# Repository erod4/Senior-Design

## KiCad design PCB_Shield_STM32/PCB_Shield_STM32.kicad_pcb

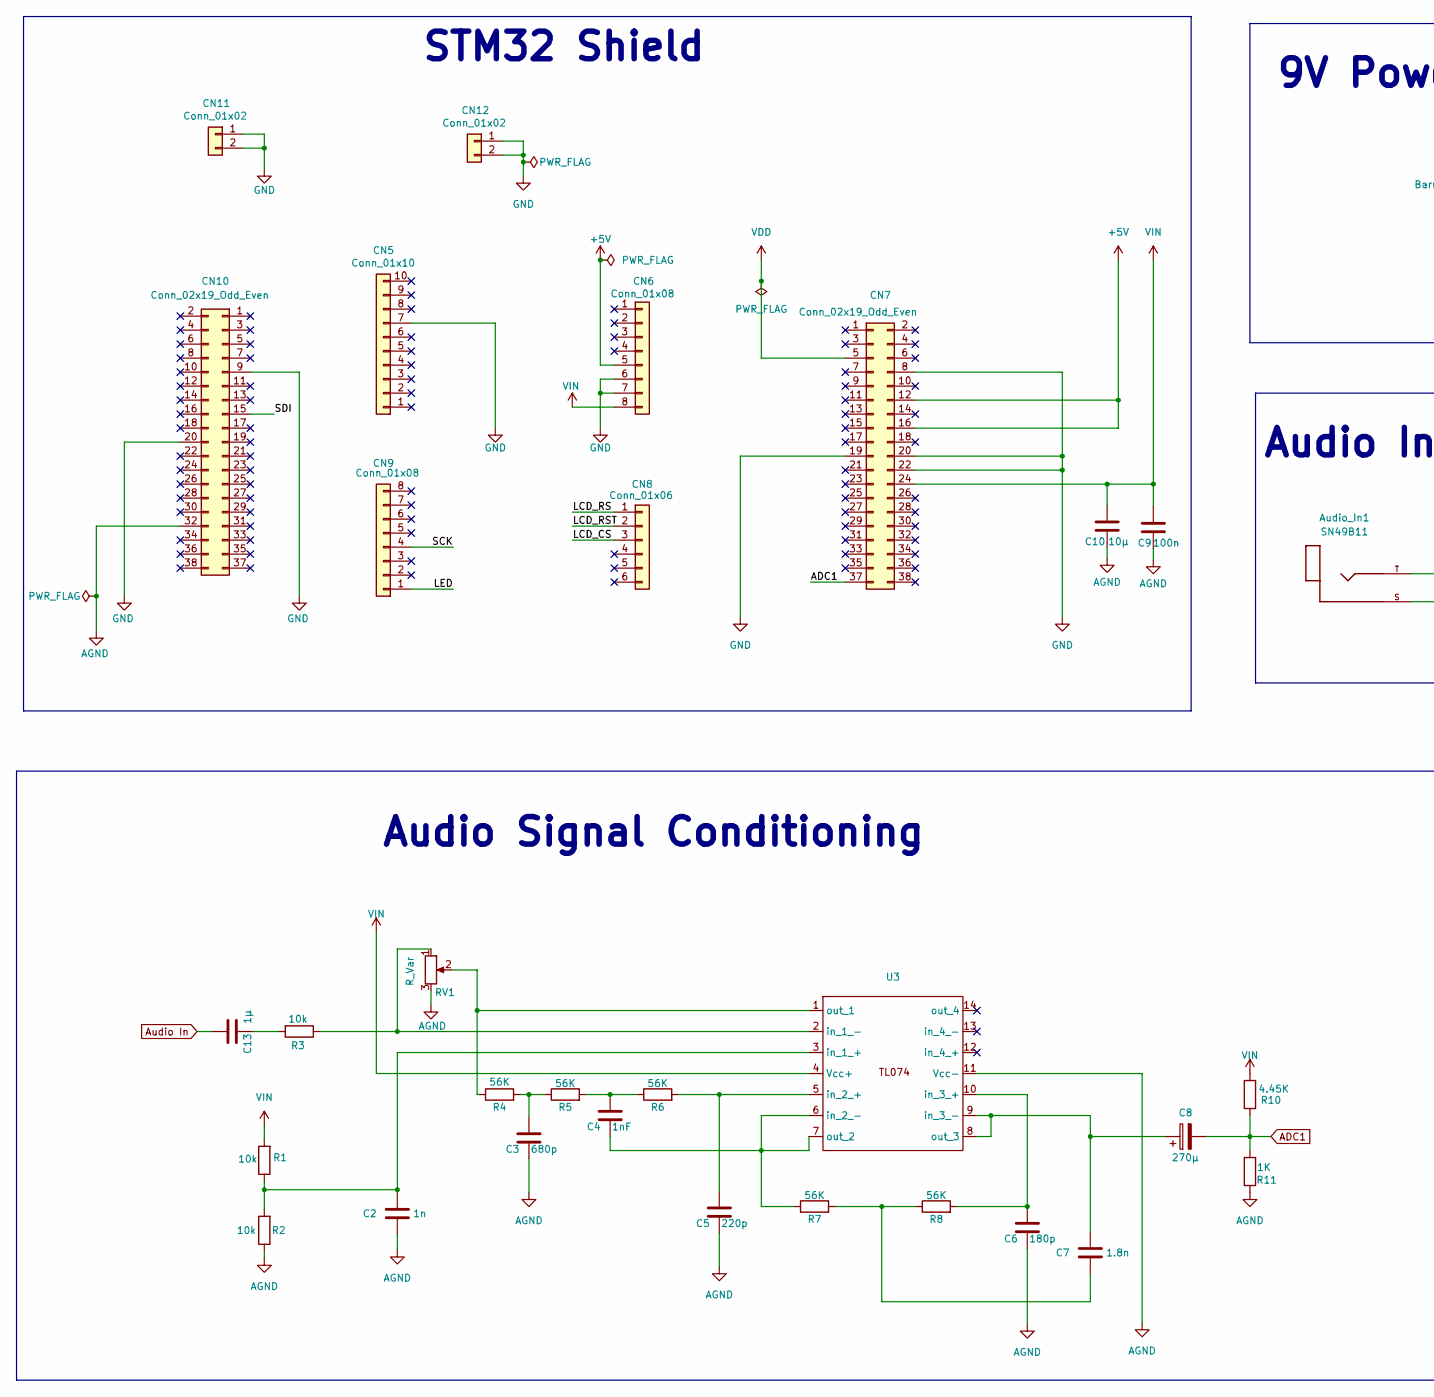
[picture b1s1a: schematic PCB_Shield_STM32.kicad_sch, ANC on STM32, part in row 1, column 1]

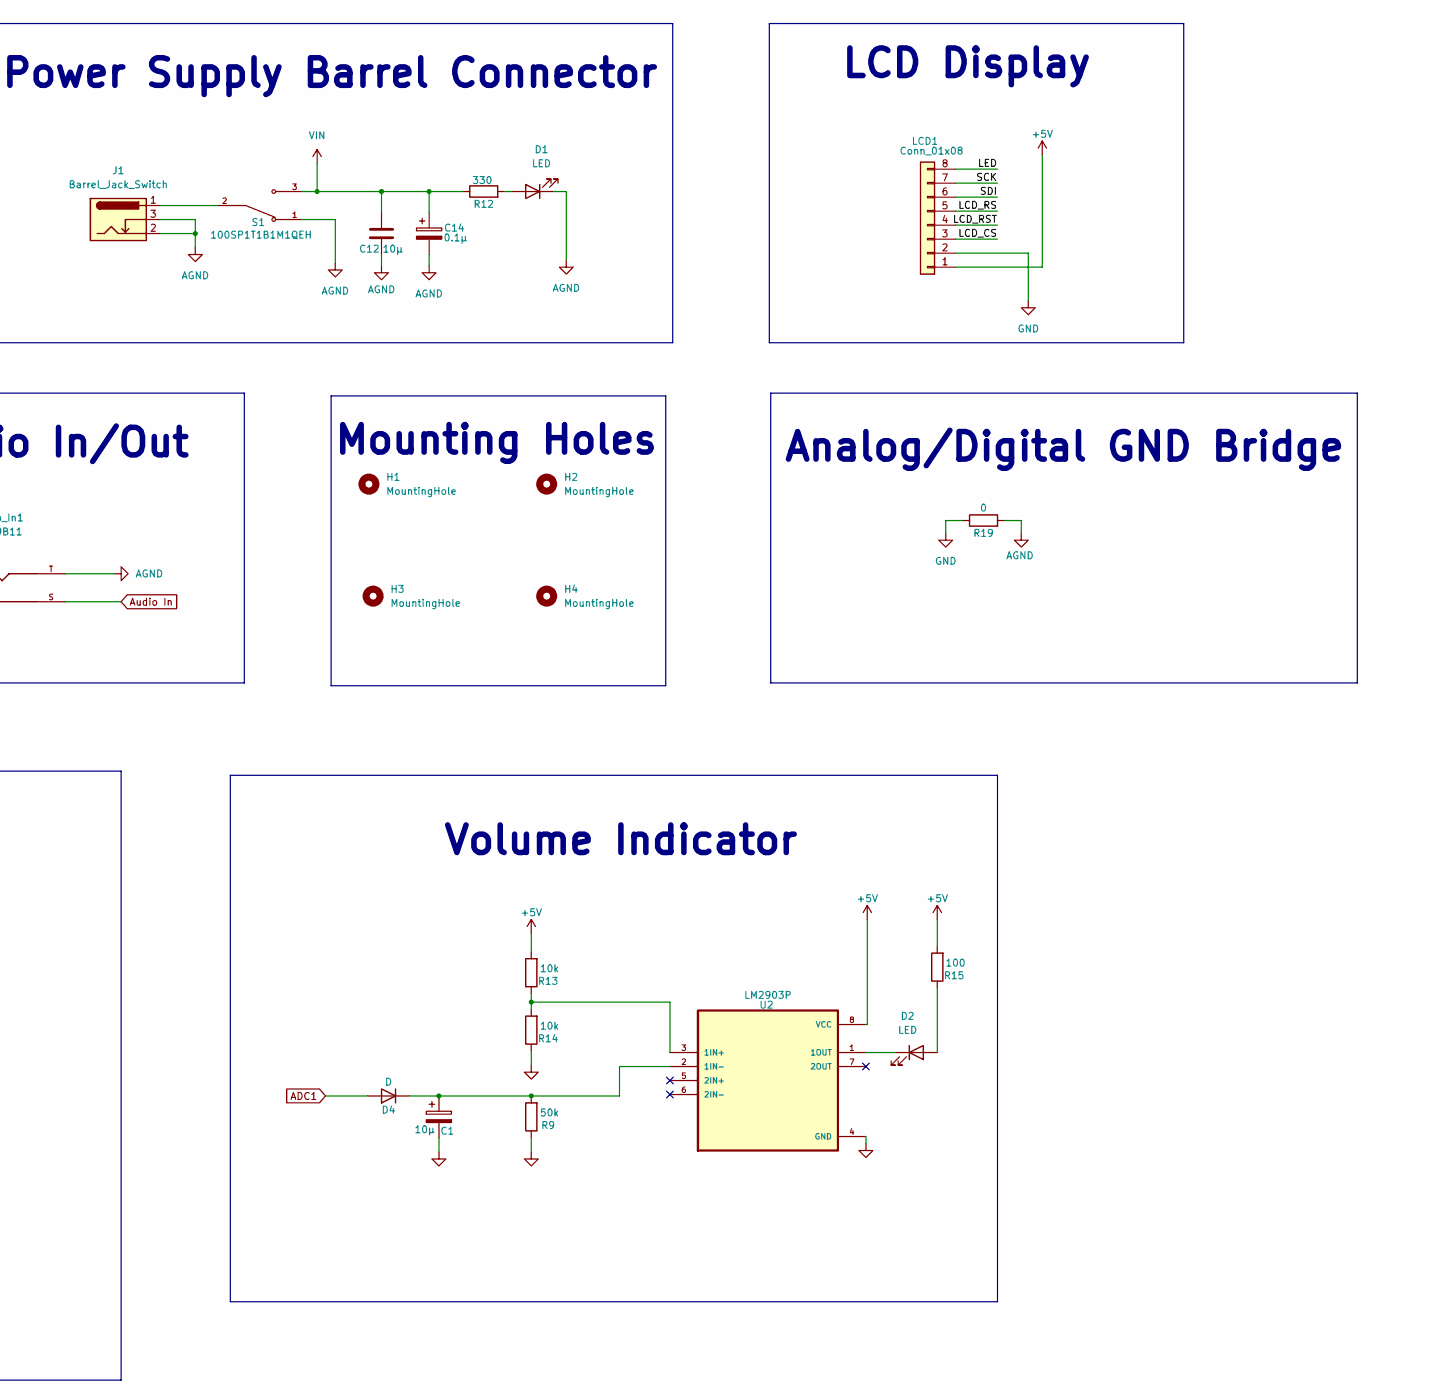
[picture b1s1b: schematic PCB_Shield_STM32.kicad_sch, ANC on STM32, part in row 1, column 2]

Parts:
Audio_In1: SN49B11; SWITCHCRAFT_SN49B11; PARTREV F
C1: 10µ; C_Radial_D4.0mm_H5.0mm_P1.50mm
C2: 1n; C_Disc_D5.0mm_W2.5mm_P5.00mm
C3: 680p; C_Disc_D5.0mm_W2.5mm_P5.00mm
C4: 1nF; C_Disc_D5.0mm_W2.5mm_P5.00mm
C5: 220p; C_Disc_D5.0mm_W2.5mm_P5.00mm
C6: 180p; C_Disc_D5.0mm_W2.5mm_P5.00mm
C7: 1.8n; C_Disc_D5.0mm_W2.5mm_P5.00mm
C8: 270µ; C_Radial_D4.0mm_H5.0mm_P1.50mm
C9: 100n; C_Disc_D5.0mm_W2.5mm_P5.00mm
C10, C12: 10µ; C_Disc_D5.0mm_W2.5mm_P5.00mm
C13: 1µ; C_Disc_D5.0mm_W2.5mm_P5.00mm
C14: 0.1µ; C_Radial_D4.0mm_H5.0mm_P1.50mm
CN5: Conn_01x10; PinSocket_1x10_P2.54mm_Vertical
CN6, CN9: Conn_01x08; PinSocket_1x08_P2.54mm_Vertical
CN7, CN10: Conn_02x19_Odd_Even; PinSocket_2x19_P2.54mm_Vertical
CN8: Conn_01x06; PinSocket_1x06_P2.54mm_Vertical
CN11, CN12: Conn_01x02; PinSocket_1x02_P2.54mm_Vertical
D1, D2: LED; LED_D3.0mm
D4: D; D_A-405_P7.62mm_Horizontal
H1, H2, H3, H4: MountingHole; MountingHole_3.2mm_M3_DIN965_Pad_TopBottom
J1: Barrel_Jack_Switch; BarrelJack_Horizontal
LCD1: Conn_01x08; PinSocket_1x08_P2.54mm_Vertical
R1, R2, R3, R13, R14: 10k; R_Axial_DIN0207_L6.3mm_D2.5mm_P7.62mm_Horizontal
R4, R5, R6, R7, R8: 56K; R_Axial_DIN0207_L6.3mm_D2.5mm_P7.62mm_Horizontal
R9: 50k; R_Axial_DIN0207_L6.3mm_D2.5mm_P7.62mm_Horizontal
R10: 4.45K; R_Axial_DIN0207_L6.3mm_D2.5mm_P7.62mm_Horizontal
R11: 1K; R_Axial_DIN0207_L6.3mm_D2.5mm_P7.62mm_Horizontal
R12: 330; R_Axial_DIN0207_L6.3mm_D2.5mm_P7.62mm_Horizontal
R15: 100; R_Axial_DIN0207_L6.3mm_D2.5mm_P7.62mm_Horizontal
R19: 0; R_Axial_DIN0207_L6.3mm_D2.5mm_P7.62mm_Horizontal
RV1: R_Var; Potentiometer_ACP_CA9-H2,5_Horizontal
S1: 100SP1T1B1M1QEH; SW_100SP1T1B1M1QEH; PARTREV D
U2: LM2903P; DIP794W45P254L959H508Q8
U3: TL074

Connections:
+5V: CN6.5, CN7.12, CN7.16, LCD1.1, R13.2, R15.2, U2.8 (VCC)
/LCD_CS: CN8.3, LCD1.3
/LCD_RS: CN8.1, LCD1.5
/LCD_RST: CN8.2, LCD1.4
/LED: CN9.1, LCD1.8
/SCK: CN9.4, LCD1.7
/SDI: CN10.15, LCD1.6
ADC1: C8.2, CN7.37, D4.2 (A), R10.1, R11.2
AGND: Audio_In1.T, C1.2, C2.2, C3.2, C5.2, C6.2, C9.1, C10.1, C12.1, C14.2, CN10.32, D1.1 (K), J1.2, J1.3, R2.1, R9.1, R11.1, R14.1, R19.2, RV1.3, S1.1, U2.4 (GND), U3.11 (Vcc-)
Audio In: Audio_In1.S, C13.2
GND: CN5.7, CN6.6, CN6.7, CN7.8, CN7.19, CN7.20, CN7.22, CN10.9, CN10.20, CN11.1, CN11.2, CN12.1, CN12.2, LCD1.2, R19.1
unnamed: C3.1, R4.2, R5.1
unnamed: C4.1, R5.2, R6.1
unnamed: C7.2, R7.2, R8.1
unnamed: C13.1, R3.2
unnamed: D1.2 (A), R12.2
unnamed: D2.2 (A), R15.1
unnamed: D2.1 (K), U2.1 (1OUT)
unnamed: C1.1, D4.1 (K), R9.2, U2.2 (1IN-)
unnamed: J1.1, S1.2
unnamed: R13.1, R14.2, U2.3 (1IN+)
unnamed: C2.1, R1.1, R2.2, U3.3 (in_1_+)
unnamed: R3.1, RV1.1, U3.2 (in_1_-)
unnamed: C5.1, R6.2, U3.5 (in_2_+)
unnamed: C4.2, R7.1, U3.6 (in_2_-), U3.7 (out_2)
unnamed: C6.1, R8.2, U3.10 (in_3_+)
unnamed: C7.1, C8.1, U3.8 (out_3), U3.9 (in_3_-)
unnamed: R4.1, RV1.2, U3.1 (out_1)
VDD: CN7.5
VIN: C9.2, C10.2, C12.2, C14.1, CN6.8, CN7.24, R1.2, R10.2, R12.1, S1.3, U3.4 (Vcc+)

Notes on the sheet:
Audio Signal Conditioning
Analog/Digital GND Bridge
LCD Display
STM32 Shield
Audio In/Out
Volume Indicator
Mounting Holes
9V Power Supply Barrel Connector

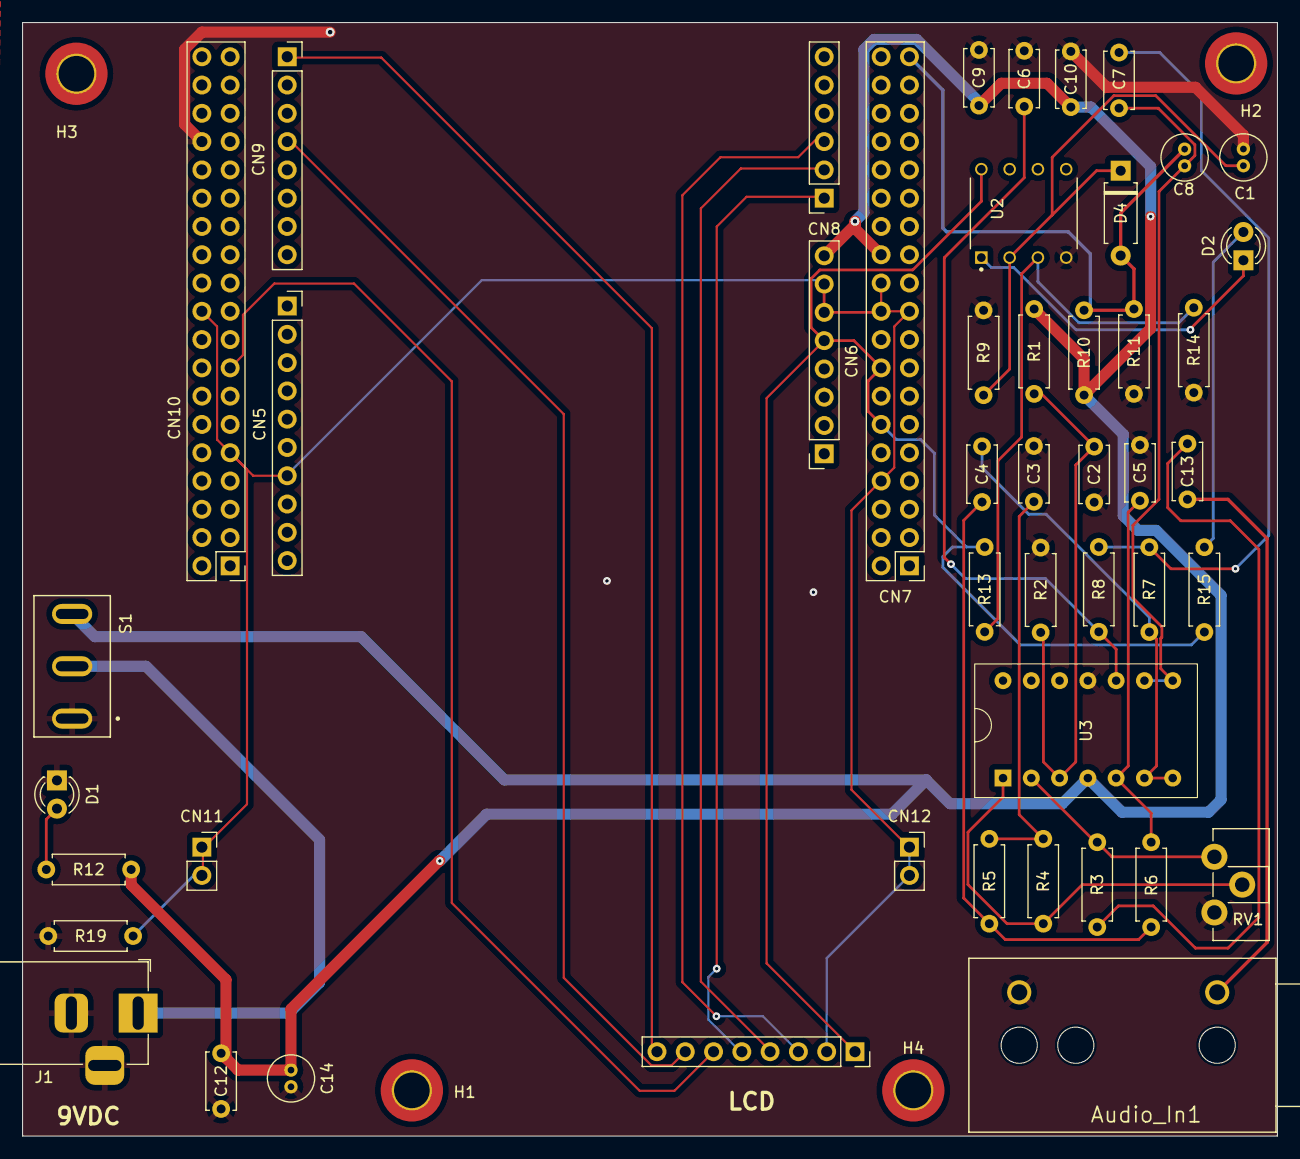
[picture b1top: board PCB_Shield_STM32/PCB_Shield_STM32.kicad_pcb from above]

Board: 2 copper layers, 112.7 x 100.0 mm, 51 parts (0 on the bottom side), 29 nets.

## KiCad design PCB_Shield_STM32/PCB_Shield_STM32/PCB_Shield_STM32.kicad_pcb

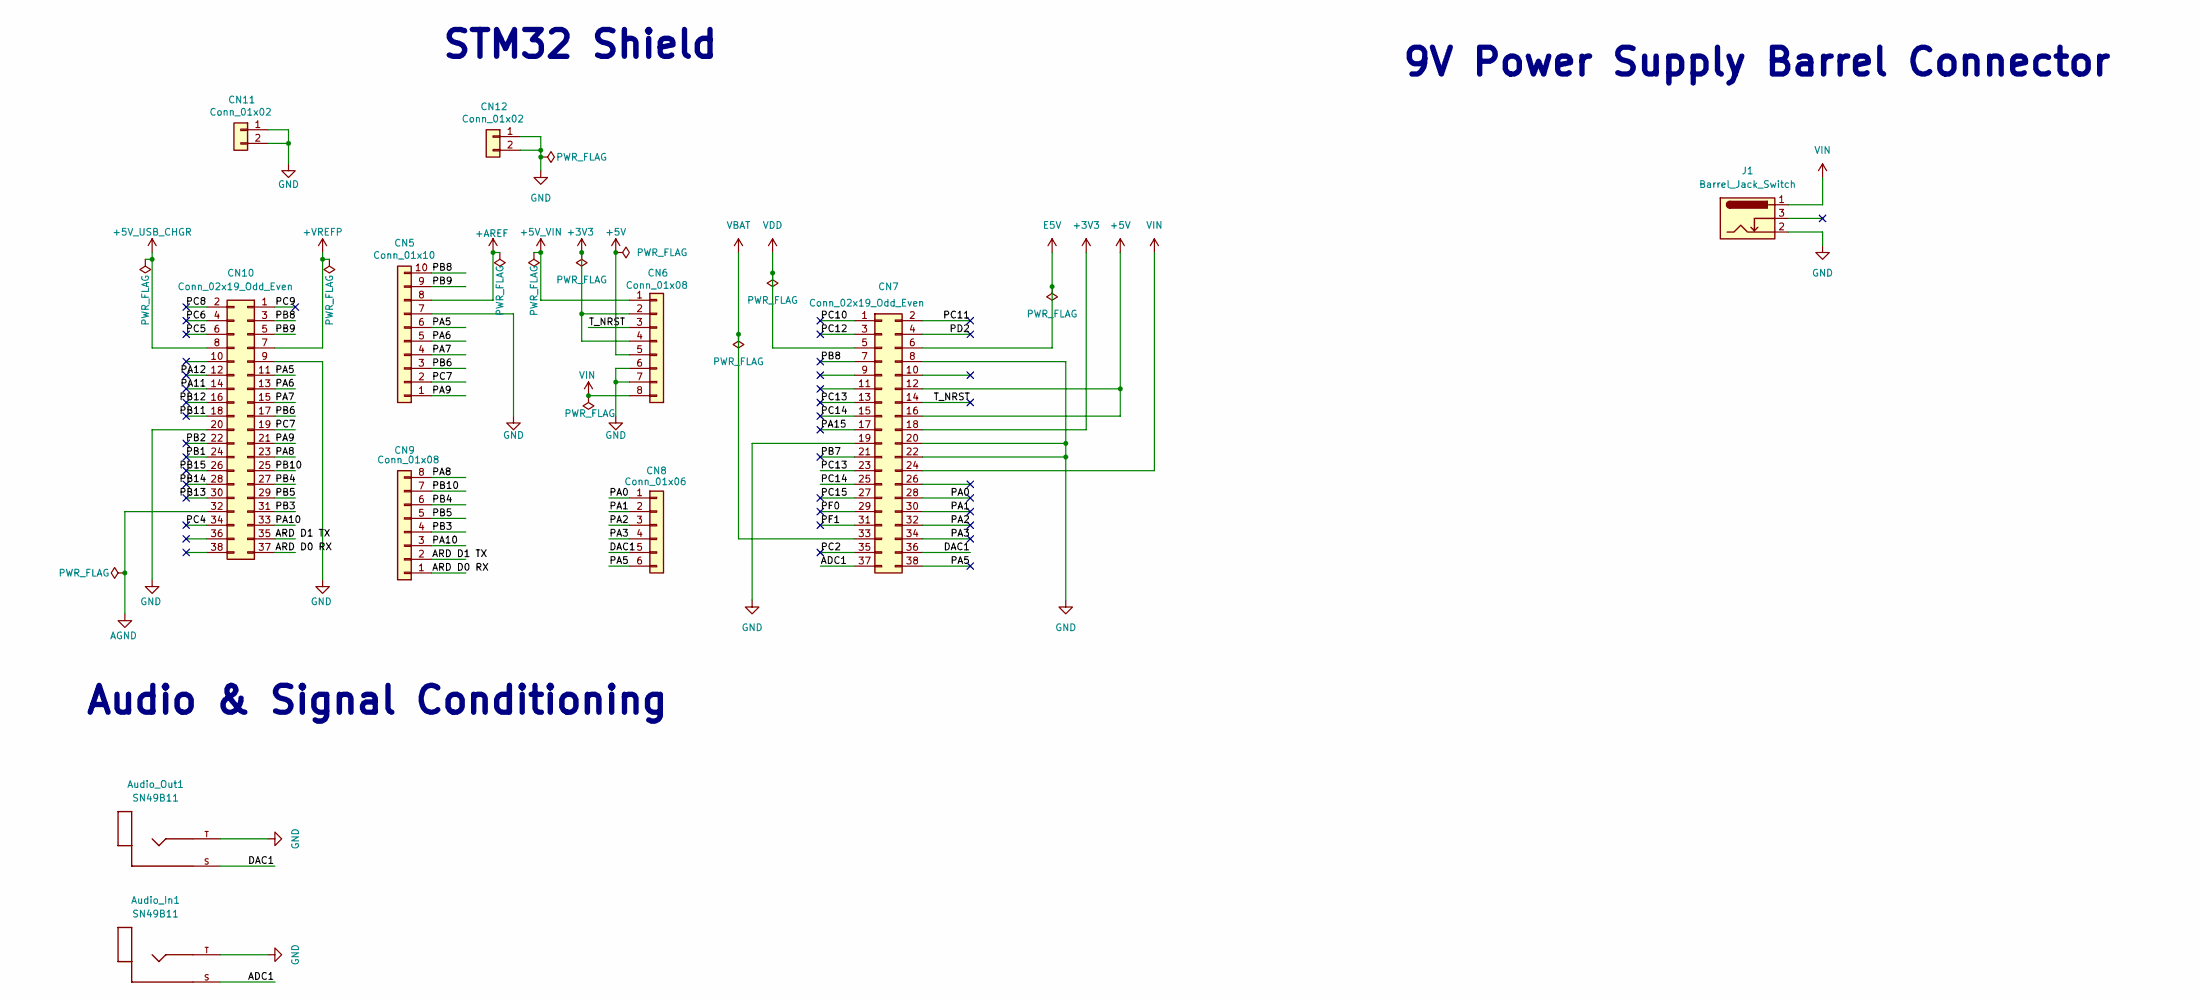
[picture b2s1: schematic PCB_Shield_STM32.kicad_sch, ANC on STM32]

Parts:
Audio_In1: SN49B11; SWITCHCRAFT_SN49B11; PARTREV F
Audio_Out1: SN49B11; SWITCHCRAFT_SN49B11; PARTREV F
CN5: Conn_01x10; PinHeader_1x10_P2.54mm_Vertical
CN6, CN9: Conn_01x08; PinSocket_1x08_P2.54mm_Vertical
CN7, CN10: Conn_02x19_Odd_Even; PinSocket_2x19_P2.54mm_Vertical
CN8: Conn_01x06; PinSocket_1x06_P2.54mm_Vertical
CN11, CN12: Conn_01x02; PinSocket_1x02_P2.54mm_Vertical
J1: Barrel_Jack_Switch; BarrelJack_Horizontal

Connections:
+3V3: CN6.2, CN6.4, CN7.18
+5V: CN6.5, CN7.12, CN7.16
+5V_USB_CHGR: CN10.8
+5V_VIN: CN6.1
+AREF: CN5.8
+VREFP: CN10.7
/ADC1: Audio_In1.S, CN7.37
/ARD D0 RX: CN9.1, CN10.37
/ARD D1 TX: CN9.2, CN10.35
/DAC1: Audio_Out1.S, CN7.36, CN8.5
/PA0: CN7.28, CN8.1
/PA1: CN7.30, CN8.2
/PA2: CN7.32, CN8.3
/PA3: CN7.34, CN8.4
/PA5: CN5.6, CN7.38, CN8.6, CN10.11
/PA6: CN5.5, CN10.13
/PA7: CN5.4, CN10.15
/PA8: CN9.8, CN10.23
/PA9: CN5.1, CN10.21
/PA10: CN9.3, CN10.33
/PA11: CN10.14
/PA12: CN10.12
/PA15: CN7.17
/PB1: CN10.24
/PB2: CN10.22
/PB3: CN9.4, CN10.31
/PB4: CN9.6, CN10.27
/PB5: CN9.5, CN10.29
/PB6: CN5.3, CN10.17
/PB7: CN7.21
/PB8: CN5.10, CN7.7, CN10.3
/PB9: CN5.9, CN10.5
/PB10: CN9.7, CN10.25
/PB11: CN10.18
/PB12: CN10.16
/PB13: CN10.30
/PB14: CN10.28
/PB15: CN10.26
/PC2: CN7.35
/PC4: CN10.34
/PC5: CN10.6
/PC6: CN10.4
/PC7: CN5.2, CN10.19
/PC8: CN10.2
/PC9: CN10.1
/PC10: CN7.1
/PC11: CN7.2
/PC12: CN7.3
/PC13: CN7.13, CN7.23
/PC14: CN7.15, CN7.25
/PC15: CN7.27
/PD2: CN7.4
/PF0: CN7.29
/PF1: CN7.31
/T_NRST: CN6.3, CN7.14
AGND: CN10.32
E5V: CN7.6
GND: Audio_In1.T, Audio_Out1.T, CN5.7, CN6.6, CN6.7, CN7.8, CN7.19, CN7.20, CN7.22, CN10.9, CN10.20, CN11.1, CN11.2, CN12.1, CN12.2, J1.2
VBAT: CN7.33
VDD: CN7.5
VIN: CN6.8, CN7.24, J1.1

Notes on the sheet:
STM32 Shield
Audio & Signal Conditioning
9V Power Supply Barrel Connector

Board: 2 copper layers, 11 parts (0 on the bottom side), 29 nets, no tracks yet.

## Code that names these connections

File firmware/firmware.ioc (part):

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Mcu.Name=STM32G491R(C-E)Tx
Mcu.Package=LQFP64
Mcu.UserName=STM32G491RETx
PA0.GPIOParameters=GPIO_Label
PA0.GPIO_Label=LCD_RS
PA0.Signal=GPIO_Output
PA1.GPIOParameters=GPIO_Label
PA1.GPIO_Label=LCD_RST
PA1.Signal=GPIO_Output
PA4.GPIOParameters=GPIO_Label
PA4.GPIO_Label=LCD_CS
PA4.Signal=GPIO_Output
PA5.Signal=COMP_DAC12_group
PA6.Mode=Full_Duplex_Master
PA6.Signal=SPI1_MISO
PA7.Mode=Full_Duplex_Master
PA7.Signal=SPI1_MOSI
PB3.Mode=Full_Duplex_Master
PB3.Signal=SPI1_SCK
PC3.Mode=IN9-Single-Ended
PC3.Signal=ADC1_IN9
RCC.HSE_VALUE=8000000
RCC.SYSCLKFreq_VALUE=170000000
RCC.SYSCLKSource=RCC_SYSCLKSOURCE_PLLCLK
board=custom

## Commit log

2024-10-20 PCB design added
2024-10-31 Timer Sampling @ 44.1KHz
2024-10-31 Added half buffer and buffer full flags in order to scale adc values to q15 and perform fft.
2024-11-03 Audio Jack in and out added.
2024-11-04 created FFT function that performs FFT and computes magnitudes and stores in output buffer.
2024-11-16 fft implementation.
2024-11-19 FFT algorithm working an tested.
2025-02-03 PCB design updated.
2025-02-13 Add files via upload
    pcb design updated
2025-02-13 updated pcb.
2025-02-20 PCB routing finalized.
2025-02-26 PCB updated.
2025-02-28 PCB V1 Finalized
2025-03-27 PCB board and firmware updated.
2025-03-27 measure wcet for lcd.
2025-03-28 LPF data graph.
2025-03-31 Create displaycode.c
    [displaycode]
    - Initializes display module
    - Draws 11 evenly-spaced bars of rainbow colors traveling up and down
    - [NEEDS] FFT data input as 'int' variables that are scaled to change the heights of the bars
2025-03-31 Organization
2025-04-14 Added latest firmware.
2025-05-13 updated firmware.
